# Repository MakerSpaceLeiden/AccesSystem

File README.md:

This directory, ACNode, needs to be copied or symbolically linked into the
libraries directory of your Arduino setup.

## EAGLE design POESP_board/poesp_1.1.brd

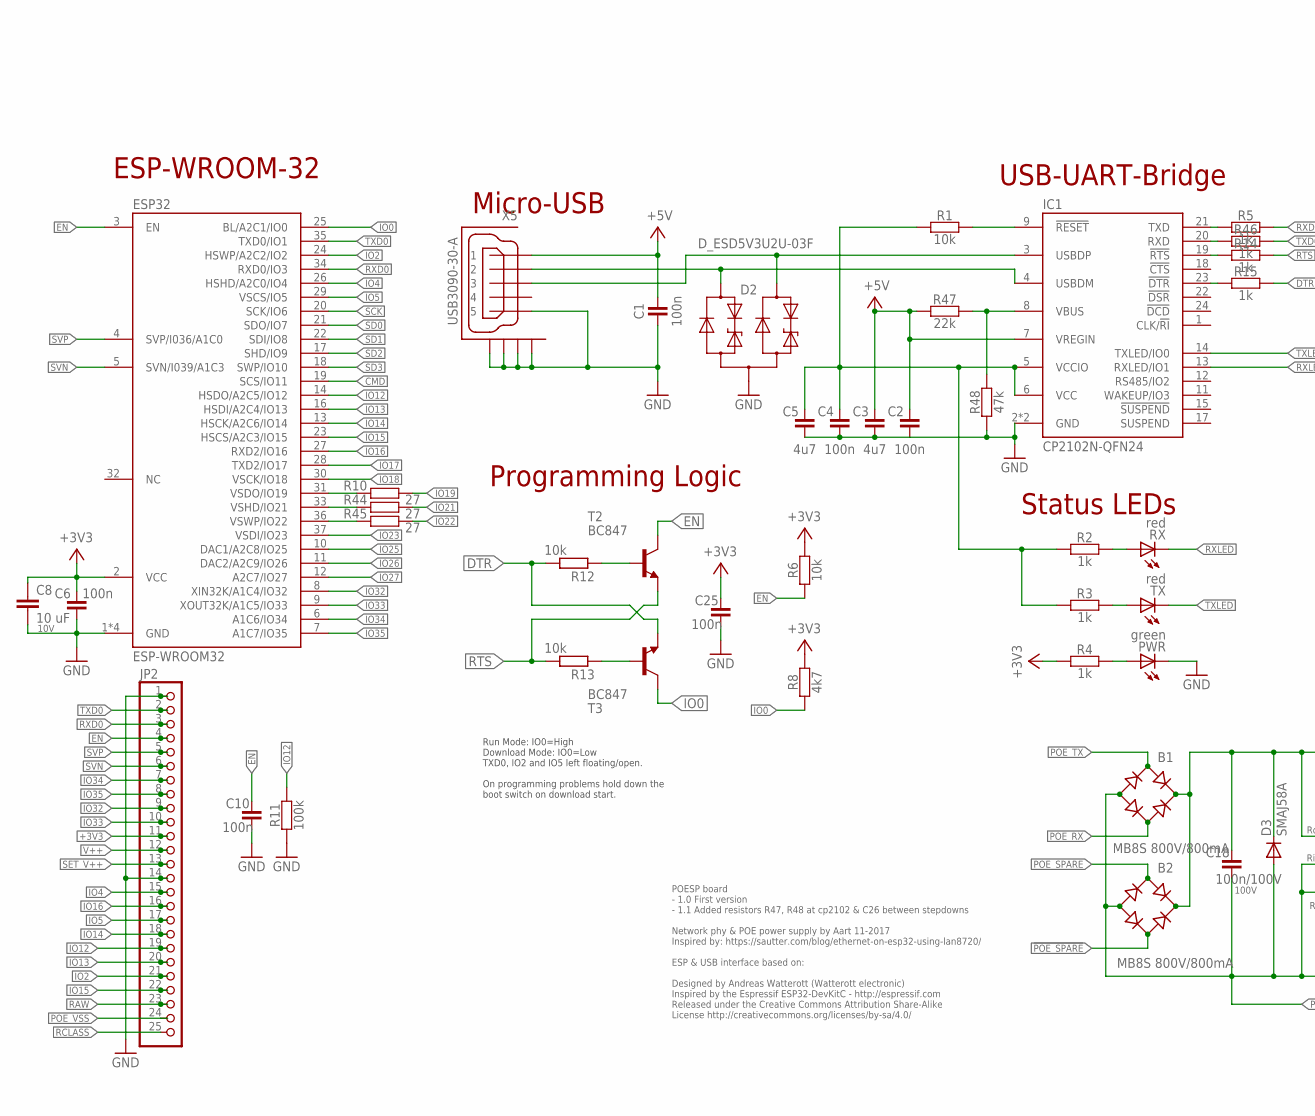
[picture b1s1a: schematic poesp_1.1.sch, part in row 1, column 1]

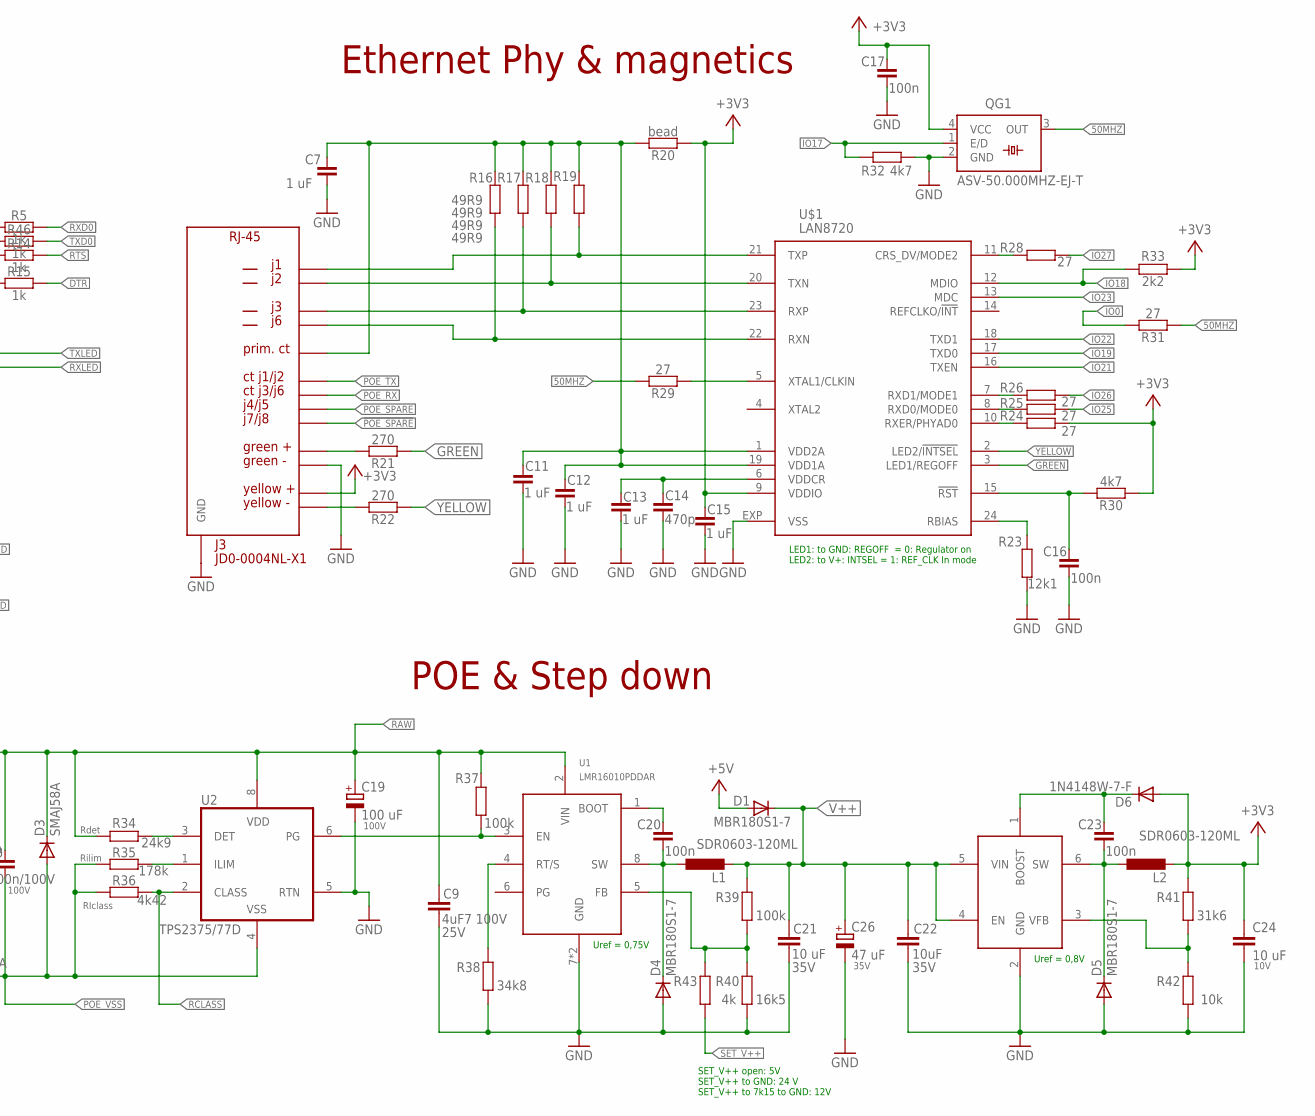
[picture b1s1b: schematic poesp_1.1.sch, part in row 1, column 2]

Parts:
B1, B2: MB8S 800V/800mA; MBS
C1, C2, C4, C6, C10, C16, C17, C20, C23, C25: 100n; C0603
C3, C5: 4u7; C0805
C7, C11, C12, C13, C15: 1 uF; C0603
C8, C24: 10 uF; C0805K; VOLTAGE 10V
C9: 4uF7 100V; C1210K; VOLTAGE 25V
C14: 470p; C0603
C18: 100n/100V; C0603; VOLTAGE 100V
C19: 100 uF; E5-10,5; VOLTAGE 100V
C21: 10 uF; C1210K; VOLTAGE 35V
C22: 10uF; C1210K; VOLTAGE 35V
C26: 47 uF; E2,5-6E; VOLTAGE 35V
D1, D4, D5: MBR180S1-7; SOD-123_MINI-SMA
D2: D_ESD5V3U2U-03F; SOT723
D3: SMAJ58A; DO214AC
D6: 1N4148W-7-F; SOD-123_MINI-SMA
ESP32: ESP-WROOM32
IC1: CP2102N-QFN24; QFN24-PAD
IC3: MCP16301/H; SOT23-6
J3: JD0-0004NL-X1; JD0
JP2: PINHD-1X25; 1X25
L1, L2: SDR0603-120ML; POWER-CHOKE_WE-TPC
PWR: green; C0603
QG1: ASV-50.000MHZ-EJ-T; SM77H
R1, R6, R42: 10k; C0603
R2, R3, R4, R5, R14, R15, R46: 1k; C0603
R8, R30, R32: 4k7; C0603
R10, R24, R25, R26, R28, R29, R31, R44, R45: 27; C0603
R11, R37, R39: 100k; C0603
R12, R13: 10k; R0603
R16, R17, R18, R19: 49R9; C0603
R20: bead; C0603
R21, R22: 270; C0603
R23: 12k1; C0603
R33: 2k2; C0603
R34: 24k9; C0603
R35: 178k; C0603
R36: 4k42; C0603
R38: 34k8; C0603
R40: 16k5; C0603
R41: 31k6; C0603
R43: 4k; C0603
R47: 22k; C0603
R48: 47k; C0603
RX: red; C0603
T2, T3: BC847; SOT23
TX: red; C0603
U1: LMR16010PDDAR; HSOIC8
U2: TPS2375/77D; SO08
U$1: LAN8720; QFN24
X5: USB3090-30-A

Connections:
50MHZ: QG1.3 (OUT), R29.2, R31.1
!POE_SPARE: B2.AC2, J3.P$8
+3V3: C6.2, C8.1, C15.2, C17.2, C24.1, C25.2, D6.A, ESP32.2 (VCC), J3.P$14, JP2.11, L2.2, QG1.4 (VCC), R4.1, R6.2, R8.2, R20.1, R24.1, R30.1, R33.1, R41.1, U$1.9 (VDDIO)
+5V: C1.2, C2.2, C3.2, D1.A, IC1.7 (VREGIN), R47.1, X5.1
CMD: ESP32.19 (SCS/IO11)
CPDTR: IC1.23 (!DTR), R15.1
CPRTS: IC1.19 (!RTS), R14.1
CPTX: IC1.21 (TXD), R5.1
DTR: R12.2, R15.2, T3.2 (E)
D_N: D2.1 (C1), IC1.4 (USBDM), X5.2
D_P: D2.2 (C2), IC1.3 (USBDP), X5.3
EN: C10.2, ESP32.3 (EN), JP2.4, R6.1, T2.3 (C)
GND: C1.1, C2.1, C3.1, C4.1, C5.1, C6.1, C7.1, C8.2, C9.2, C10.1, C11.1, C12.1, C13.1, C14.1, C15.1, C16.1, C17.1, C19.-, C21.2, C22.2, C24.2, C25.1, C26.-, D2.3 (A), D4.A, D5.A, ESP32.1 (GND), ESP32.15 (GND), ESP32.38 (GND), ESP32.TP (GND), IC1.2 (GND), IC1.TP (GND), IC3.2 (GND), J3.P$11, J3.P$21 (GND), J3.P$22 (GND), J3.P$23 (GND), J3.P$24 (GND), JP2.1, JP2.14, PWR.C, QG1.2 (GND), R11.1, R23.1, R32.1, R38.2, R40.2, R42.2, R48.1, U1.7 (GND), U1.P$9 (GND), U2.5 (RTN), U$1.EXP (VSS), X5.5, X5.GND2 (GND1), X5.GND3 (GND2), X5.P$1 (GND3), X5.P$2 (GND4)
GREEN: R21.1, U$1.3 (LED1/REGOFF)
IO0: ESP32.25 (BL/A2C1/IO0), R8.1, R31.2, T3.3 (C)
IO2: ESP32.24 (HSWP/A2C2/IO2), JP2.21
IO4: ESP32.26 (HSHD/A2C0/IO4), JP2.15
IO5: ESP32.29 (VSCS/IO5), JP2.17
IO12: ESP32.14 (HSDO/A2C5/IO12), JP2.19, R11.2
IO13: ESP32.16 (HSDI/A2C4/IO13), JP2.20
IO14: ESP32.13 (HSCK/A2C6/IO14), JP2.18
IO15: ESP32.23 (HSCS/A2C3/IO15), JP2.22
IO16: ESP32.27 (RXD2/IO16), JP2.16
IO17: ESP32.28 (TXD2/IO17), QG1.1 (E/D), R32.2
IO18: ESP32.30 (VSCK/IO18), R33.2, U$1.12 (MDIO)
IO19: R10.1, U$1.17 (TXD0)
IO21: R44.1, U$1.16 (TXEN)
IO22: R45.1, U$1.18 (TXD1)
IO23: ESP32.37 (VSDI/IO23), U$1.13 (MDC)
IO25: ESP32.10 (DAC1/A2C8/IO25), R25.1
IO26: ESP32.11 (DAC2/A2C9/IO26), R26.1
IO27: ESP32.12 (A2C7/IO27), R28.1
IO32: ESP32.8 (XIN32K/A1C4/IO32), JP2.9
IO33: ESP32.9 (XOUT32K/A1C5/IO33), JP2.10
IO34: ESP32.6 (A1C6/IO34), JP2.7
IO35: ESP32.7 (A1C7/IO35), JP2.8
unnamed: J3.P$1, R19.1, U$1.21 (TXP)
unnamed: J3.P$2, R18.1, U$1.20 (TXN)
unnamed: J3.P$3, R17.1, U$1.23 (RXP)
unnamed: J3.P$5, R16.1, U$1.22 (RXN)
unnamed: C7.2, C11.2, C12.2, J3.P$4, R16.2, R17.2, R18.2, R19.2, R20.2, U$1.1 (VDD2A), U$1.19 (VDD1A)
unnamed: R23.2, U$1.24 (RBIAS)
unnamed: C16.2, R30.2, U$1.15 (!RST)
unnamed: C13.2, C14.2, U$1.6 (VDDCR)
unnamed: J3.P$12, R21.2
unnamed: IC1.8 (VBUS), R47.2, R48.2
unnamed: J3.P$13, R22.2
unnamed: R38.1, U1.4 (RT/S)
unnamed: R28.2, U$1.11 (CRS_DV/MODE2)
unnamed: R26.2, U$1.7 (RXD1/MODE1)
unnamed: R24.2, U$1.10 (RXER/PHYAD0)
unnamed: R34.1, U2.3 (DET)
unnamed: R35.1, U2.1 (ILIM)
unnamed: R25.2, U$1.8 (RXD0/MODE0)
unnamed: R29.1, U$1.5 (XTAL1/CLKIN)
unnamed: C4.2, C5.2, IC1.5 (VCCIO), IC1.6 (VCC), R1.1, R2.1, R3.1
unnamed: C20.2, U1.1 (BOOT)
unnamed: C20.1, D4.C, L1.1, U1.8 (SW)
unnamed: R37.2, U1.3 (EN), U2.6 (PG)
unnamed: R13.1, T3.1 (B)
unnamed: C23.1, D5.C, IC3.6 (SW), L2.1
unnamed: R39.2, R40.1, R43.1, U1.5 (FB)
unnamed: R12.1, T2.1 (B)
unnamed: ESP32.31 (VSDO/IO19), R10.2
unnamed: ESP32.33 (VSHD/IO21), R44.2
unnamed: IC3.3 (VFB), R41.2, R42.1
unnamed: ESP32.36 (VSWP/IO22), R45.2
unnamed: IC1.20 (RXD), R46.1
unnamed: C23.2, D6.C, IC3.1 (BOOST)
POE_RX: B1.AC2, J3.P$10
POE_SPARE: B2.AC1, J3.P$7
POE_TX: B1.AC1, J3.P$9
POE_VSS: B1.-, B2.-, C18.1, D3.A, JP2.24, R35.2, R36.2, U2.4 (VSS)
PWR-LED: PWR.A, R4.2
RAW: B1.+, B2.+, C9.1, C18.2, C19.+, D3.C, JP2.23, R34.2, R37.1, U1.2 (VIN), U2.8 (VDD)
RCLASS: JP2.25, R36.1, U2.2 (CLASS)
RESET: IC1.9 (!RESET), R1.2
RTS: R13.2, R14.2, T2.2 (E)
RX-LED: R2.2, RX.A
RXD0: ESP32.34 (RXD0/IO3), JP2.3, R5.2
RXLED: IC1.13 (RXLED/IO1), RX.C
SCK: ESP32.20 (SCK/IO6)
SD0: ESP32.21 (SDO/IO7)
SD1: ESP32.22 (SDI/IO8)
SD2: ESP32.17 (SHD/IO9)
SD3: ESP32.18 (SWP/IO10)
SET_V++: JP2.13, R43.2
SVN: ESP32.5 (SVN/I039/A1C3), JP2.6
SVP: ESP32.4 (SVP/I036/A1C0), JP2.5
TX-LED: R3.2, TX.A
TXD0: ESP32.35 (TXD0/IO1), JP2.2, R46.2
TXLED: IC1.14 (TXLED/IO0), TX.C
V++: C21.1, C22.1, C26.+, D1.C, IC3.4 (EN), IC3.5 (VIN), JP2.12, L1.2, R39.1
YELLOW: R22.1, U$1.2 (LED2/!INTSEL)

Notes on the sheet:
POESP board - 1.0 First version - 1.1 Added resistors R47, R48 at cp2102 & C26 between stepdowns Network phy & POE power supply by Aart 11-2017 Inspired by: https://sautter.com/blog/ethernet-on-esp32-using-lan8720/ ESP & USB interface based on: Designed by Andreas Watterott (Watterott electronic) I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
USB-UART-Bridge
Micro-USB
Status LEDs
Programming Logic
ESP-WROOM-32
Run Mode: IO0=High Download Mode: IO0=Low TXD0, IO2 and IO5 left floating/open. On programming problems hold down the boot switch on download start.
LED1: to GND: REGOFF = 0: Regulator on LED2: to V+: INTSEL = 1: REF_CLK In mode
Ethernet Phy & magnetics
POE & Step down
Uref = 0,75V
Uref = 0,8V
SET_V++ open: 5V SET_V++ to GND: 24 V SET_V++ to 7k15 to GND: 12V

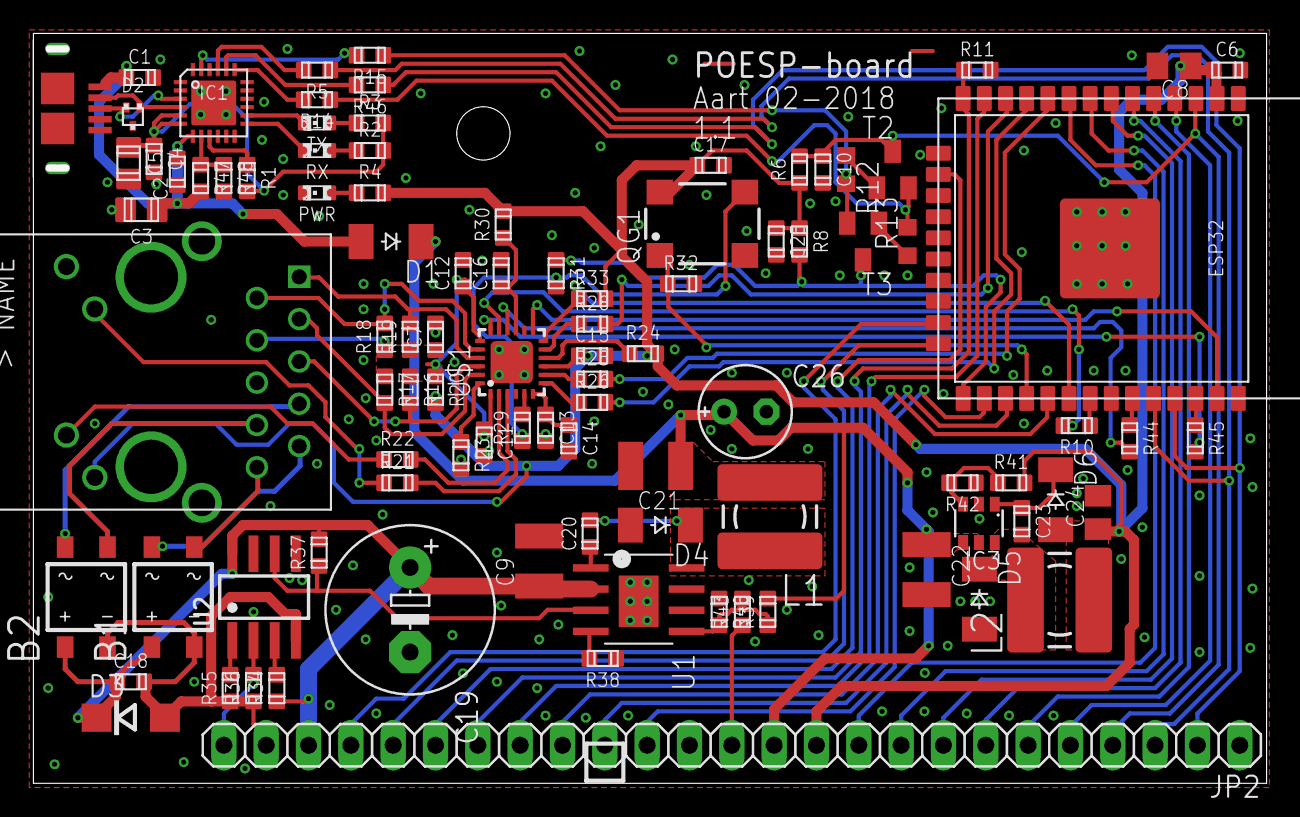
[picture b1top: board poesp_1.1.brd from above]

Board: 2 copper layers, 73.6 x 44.6 mm, 96 parts (0 on the bottom side), 88 nets.

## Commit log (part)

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2018-10-28 More agressive resync and 2 way welcome.
2018-10-29 RFID SPI test with the settings from the wiki.
2018-10-30 Test cases for some of the RFID hardwar.
2018-10-30 Centralize LEDs, remove blinken.
2018-10-30 Removed OSX specific buiild
2018-10-31 Further simplifiction of above the waterline app code.
2018-11-01 Updated test, simplified api.
2018-11-01 Security protocols need to be initialised earlier.
2018-11-01 Fix edge cases.
2018-11-01 Last version test board.
2018-11-02 Various tweaks & moving all into SIG2 class.
2018-11-05 Caching, cleanup rfid code.
2018-11-06 Fix caching
2018-11-11 Minor tweals; add debouncing
2018-11-11 TOFU persistance.
2018-11-15 Add reporting, tweak logging load and backoff.
2018-11-15 More reporting.
2018-11-16 Remove second set of current check; rely on callbacks.
2018-11-21 changed to start with Fan ON, but does not compile - missing AES256.h and maybe others
2018-11-22 Keep track of memory - as we got hit by https://github.com/espressif/esp-idf/issues/774.
2018-11-22 Simple node; auto-generate a unique name if none is set; but more reporting on macaddresses and ips.
2018-11-23 Tweaking reporting output
2018-11-24 Rework and modernise extractor fan example.
2018-11-24 fix bracket.
2018-11-24 More examples, further simplification of above the line code.
2018-11-24 ping ping example
2018-11-30 First handle state change - then check timeout (so that the latter does not see the state in-btween and ackts wrong (e.g. on swipe)
2018-12-09 start of wifi-planer node.
2018-12-09 Make the LED static state pattern more recognizable.
2018-12-09 Update for new crypto lib.
2018-12-09 Quell compiler warning; log actual moment power comes on.
2018-12-14 Version as put into the planer board
2018-12-23 Reintrduce EPS8266 support; DeWaltNode (not tested/compiled yet).
2018-12-23 Fully functional on ESP 8266
2018-12-24 Remove wrongly added tmp file vi.
2019-01-12 negate check - as we've changed the wiring
2019-01-28 Doors as currently deployed.
2019-01-29 As currently deployed across all machines.
2019-02-07 As deployed
2019-02-08 As deployed.
2019-03-10 Hardware checks out
2019-03-11 test versions for the Bye Bye node - and empty start of the production code for the node with baseline leave functionality.
2019-04-27 Tighten security, test script SQL
2019-05-04 As currently deployed in the node on the door.
2019-05-05 As currently deployed (with faster scroll speed)
2019-05-17 Split .h's to override partially later
2019-09-08 Tiny tweaks with latest Arduino IDE, add mainsSensor code.
2019-10-02 Simple sample node without reader, etc. not tested.
2019-10-09 Fix for 1.8.10 - mainly replacing NULL by nullptr for the function points; no longer rely on dynamic case/switch blocks and modernise includes to match lates version of rweather/arduinolibs.
2019-10-09 Partial switch to REST
2019-10-09 Minor tweak for python 3.7 / 3.6 -- as one does add an extra (correct) == to the base64.
2019-10-10 Introduce parallel trust
2019-10-11 Migratie van json5 -> 6
2019-10-11 Update GPIO pin to pin actually used according to the wiki.
2019-10-12 Clarify root/non-root
2019-10-12 Proactively (re)subscribe on each loss/regain of the networ for the trusted channels.
2019-10-15 Mostly remove coupling with SQL - to go to full rest asap
2019-10-18 Correct GIT url for automatic build.
2019-10-19 Move around states for the manchine-state enum - to get rudimentary extensibility
2020-01-18 start of merging in chages for grote schakelaar
2020-01-18 Version as currently deployed.
2020-01-25 Shuffle repository - legacy moved away (post 2020 network cleanup).
2020-01-25 Suppress debug output
2020-01-26 Also move python libs
2020-02-02 Quell warning
2021-12-16 Tweaks for Arduino 2.0.x
2022-02-08 Tentative caching fix - homebuild ULong parse.
2022-02-08 As pushed to tussendeur
2022-02-08 Also do some negative caching.
2022-02-09 Remove dependency on Arduino Base64.hpp - as it's lack of a .c/.cpp gives linker errors when used in multiple places; switch to the Espressif/mbed-tls included base64.
2022-02-09 Remove all logging code; rely on T-Log
2022-02-17 Change to what arduino usually outputs
2022-02-17 Neutral test node
2022-02-17 Correct time
2022-02-17 Add some extra debugging info on fails.
2022-02-18 Tweak text; include the terminating \0 count in strncat correctly.
2022-02-18 Fix order to make init quicker, fix to v2 of the JSOn dynamic API, reroute logging.
2022-02-18 Modernize/remove most code from Spacedeur - and add some convenience overlaoding
2022-12-27 Add cabinet node for saw blades locker
2023-05-16 Snapshot of production; avoid log files from growing and prevent crash on wrongly formatted signature
2023-11-10 Start branch to merge code from Hans for i2c expander, new type of RFID and extra capabilities
2023-11-12 Remove deps on legacy AES/CBC
2023-11-13 New 0.9 board; not quite able to kill al legacy crypto
2023-11-13 Remove legacy alterantive
2023-11-13 Document source for this NFC module (https://github.com/Seeed-Studio/PN532)
2023-11-14 Try making the reset more functional; esp. as Wire() fiddling appears to cause i2c breakage across no powercycling reboots.
2023-11-15 Ready code for i2c expander
2023-11-15 Remove legacy Curve:: calls completely.
2023-11-15 Removed the final dependecy on RNG from Aduino Crypto.
2023-11-28 Re-enable wiping function
2023-11-28 Work in progress; mapping to MCP
2023-12-07 End to end working; not all NodeNG changes folded back in.
2023-12-09 Pospone countdown; so it clearer what is happening on 'non use'
2023-12-10 Start for Mitrsawnode in welding area; including pump prompting
2023-12-12 Tweaks for NG and White; update of Bandswaw/Woodl for rollout
2023-12-13 Prevent clashes; be explicit about the timeout to make finding misconfiguration easier
2023-12-14 Make the default name log rather than logs.
2023-12-16 Add an auto-soft reset if the version # cannot be read for extended periods of time
2023-12-21 Move screen and state logic down into the libary to empty out the Mitre Saw as the first example
2023-12-21 Work around for the c11++/c lambda not having XS to locals
2023-12-22 Start with adding a permit feature
2023-12-24 Simplyfy one node; move OTA so that we can get an update shown on the screen -and- prevent it from happening when the machine is in use (not tested yet
2024-01-01 Pass at a few nodes.
2024-01-01 Disable screen on WoodLathe - which has no screen...
2024-01-02 Draft for Lintzaag. Added time
2024-01-06 Tweaks to on/off process and more instructions on the screen.
2024-02-09 minor cleanups
2024-05-24 Functional
2024-05-25 Working monitoring
2024-08-20 Update for newer boards
2024-09-08 mid edits
2024-09-08 e2e tested on v111
2024-09-08 Remove osx cruft
2024-09-11 Working with experimental version BIN
2024-09-14 Tweaks for display/deck, not yet complete
2024-09-19 functional baseline; OTA tested; decks tested, no reporting back yet
2024-09-21 Fix order, OTA, freezeout for firmware updates, non-alloc display. Add Start of JWT tokens
2024-09-22 cleanup io, add prssure sensor, move eeprom out
2024-09-25 Cleanups for pressure sensure; tweak display; change valve logic
2024-09-26 Tweak detection and Wire read of pressure sensor
2024-09-29 Minor tweaks; most UI related.
2024-10-01 Simplify deckCtrl, clarify main text.
2024-10-02 Added notifcation
2024-10-04 Minor tweaks
2024-10-08 Tweaks to pressure
2024-10-08 In case thigns happen at the same time
2024-10-31 Reduce debugging output; add strawman for claims
2024-12-01 Fix date, add counter on denied
2024-12-07 Avoid revealing tag in common setting
2024-12-30 new MSL logo
2025-02-10 Various, mostly cosmetic tweaks; version readied for bandsaw node replacemnt
2025-02-10 Add debug, make defaults route sensible
2025-02-13 Fix missing tickers; allow for nodes without a NC wire (orange wire)
2025-05-21 Also show GW and DNS to track doen current routing issue tussendeur
2025-05-24 As rolled out to spacedeur
2025-05-26 Repair tickets; disable red flashes on newer nodes
2025-05-27 With end stopper
2025-06-04 Introduce some more randomness; e.g for when all units reboot due to a power cut
2025-06-05 Engraver; tested with board #15
2025-06-05 Fix url of wiki
2025-06-06 Fix the actual name
2025-06-14 Fix disconnected mqtt handling (or do an attempt thereof)
2025-08-24 Attempt at resolving merge conflicts
2025-09-09 Fix update intervals
2025-09-10 Modernise OTA
2025-09-10 Allow for handlers to have a name to aid debugging/profiling. Add the error LED to a handler to allow the heartbeat to also work if there is no timer available/assigned.
2025-09-15 Remove delayed state engine; go back to 'direct' again
2025-09-15 Clean up formatting
2025-09-15 Remove tickets completely; they wreak havoc with the broken semaphores when we use Adafruit libs.
2025-09-15 Change confusing text on display
2025-09-28 Disable Seed version of the PN532 reader; it is no longer compatible with 3.3.1 & we possibly are no longer user it anywhere
2025-09-28 Simple singleton for randomness; now newer MBEDTLS routines require this as an argument
2025-09-28 Update all APi calls to the more modern 3.2 ones.
2025-09-29 adapt to mbedtls 3.x api
    some functions dropped their _ret suffix
    ECDH context was refactored, and fields were marked private by adding _private suffix. macros were added to keep access to those fields succinct.
2025-10-09 move reporting around to reduce code; split out binary file parsing so it can be tested separate from the ESP32 code again.
2025-10-10 Fix various debug message, clarify errors if cache goes wrong, make profile easier to read
2025-10-11 Add buzzer, tweaks to make things work end to end
2025-10-12 Initial implementation for new trash node
2025-10-16 Modernise planer, circle saw and jointer. Update for new OTA type, start with caching payment data
2025-10-18 Tweaks display - still not right
2025-10-29 Reduce output
2025-11-11 Simplify code
2025-11-12 Door to kitchen
2025-11-13 Fix md5/sha256 password hash issue
2025-12-12 Start of code for outside door Olga complex
2025-12-13 Add red/blue button test olga doors
2025-12-14 Add i2c detect, make display dis-ableable, get the names right, expose actual class used
2025-12-14 Increase current a little - to brighten up leds in buttons
2025-12-14 Add json reports & display as URLs
2025-12-24 Reduce stack footprint, increase stack size, reduce large mallocs, remove copys during reporting
2025-12-24 Reduce stack szie; pick up NTP from DHCP where available
2025-12-25 start of display page
2025-12-26 Minor tweaks & cleanups
2025-12-30 Minor tweaks (bijknagen) to make things work with an older node
2026-01-01 Start of pNG option - test
2026-01-04 Start of a simple kiosk login for olga
2026-01-05 Also allow 201 created
2026-01-05 Nibbling the UI in shape, no real changes
2026-01-10 Fix length; cutting of full names needlessly
2026-01-11 Switch to ENUM to help the compiler catch errors - as CHANGE is used differently by different libraries in teh Arduino eco system
2026-01-15 Tweak display/status a bit for easier parsing
2026-01-29 Reduce includes, make the reset hard and add a reset for the rfid via hardware pulldown.
2026-01-29 Add debugging during reporting; usefule to debug mqtt bulk problems
2026-02-11 Reduce speed further; add reset/selftest option to debug in situ
2026-02-28 tweaks to debug AW
2026-02-28 As currently in the keet deur
2026-05-10 Also expose some user info on HTTP (same as on MQTT)
2026-05-11 Student node; fix reporting and syntax
2026-05-19 Tweak for students; add also webseocket on state to experiment.
2026-05-20 Fix renaming:
2026-05-20 Remove debugging statement that is confusing/not always correct
2026-05-28 Align with new (and hopefully stable) location of RTC API
2026-05-28 Add a feature to expose more state to the students, part 1
2026-05-28 Add simple state reporting
2026-06-02 new static allocator for jsons
2026-06-02 Document extra pin/button for the newer boards
2026-06-02 Move memory for json

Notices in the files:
POESP_board/poesp_1.1.sch:
Released under the Creative Commons Attribution Share-Alike
License http://creativecommons.org/licenses/by-sa/4.0
parts and their libraries:
microchip-smsc-lan8720: (C) 2014 Tomasz Boleslaw CEDRO, cederom@tlen.pl, http://www.tomek.cedro.info.
